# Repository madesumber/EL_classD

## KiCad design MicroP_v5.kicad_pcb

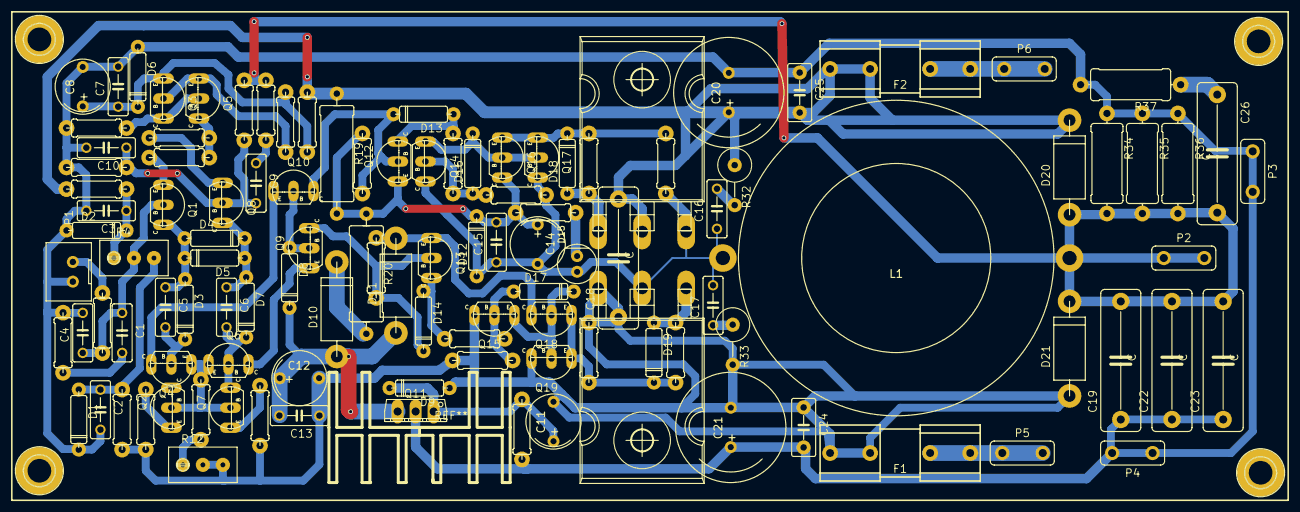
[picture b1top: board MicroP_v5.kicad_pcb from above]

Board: 2 copper layers, 114 parts (0 on the bottom side), 52 nets.

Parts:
C1, C2, C3, C4, C5, C6, C7, C9, C10, C13, C15, C16, C17: C; C050-025X075
C8, C11, C12, C14: CP; CP_5mm
C18, C19, C22, C23, C26: C; C-X2-150-054X183
C20, C21: CP; CP_5mm_14mm
C24, C25: C; C050-030X075
D1, D2, D6, D8, D9, D12: D_Schottky; DIODE_7.62mm
D3, D4, D5, D7, D13, D14, D16, D17, D18, D19: D; DIODE_7.62mm
D10, D11, D20, D21: D; Diode-3A
D15: Led_Small; LED
F1, F2: FUSE; Fuse-holder1
L1: INDUCTOR; Core_T157
P1: IN; CON-XH-2pin
P2, P3, P4, P5, P6: CONN_01X01; SKUN_TAB_PCB
Q1, Q3, Q5, Q8, Q12, Q13, Q14, Q15, Q17, Q19: BC557; TO92-321_EBC
Q2, Q4, Q6, Q7, Q9, Q10, Q16, Q18: BC547; TO92-321_EBC
Q11: TIP120; TO126V
Q20, Q21: IRF540N; TO247BH-123_GDS
R1, R2, R3, R5, R6, R7, R8, R9, R10, R11, R13, R14, R15, R16, R17, R18, R21, R22, R23, R24, R25, R26, R27, R28, R29, R30, R31: R; R0207-7
R4, R12: TRIM; R-TRIM3296W
R19, R20: R; R0414-15
R32, R33: R; R0617V
R34, R35, R36, R37: R; R0411-12

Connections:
GND: C2.2, C3.2, C4.2, C7.2, C8.2, C10.2, C19.1, C20.2, C21.1, C22.1, C23.1, C24.2, C25.1, D1.1, D2.2, D6.2, P1.1, P3.1, P4.1, Q11.2, R2.1, R6.1, R16.2, R18.1, R34.1, R35.1, R36.1, R37.2
unnamed: C1.1, C4.1, Q1.2, R1.2, R4.2
unnamed: C1.2, R2.2
unnamed: C2.1, D1.2, R4.3, R5.2
unnamed: C3.1, D2.1, R3.1, R4.1
unnamed: C5.1, D3.2, D4.2, D5.1, Q1.1
unnamed: C5.2, D3.1, Q2.1, Q4.2
unnamed: C6.1, D4.1, D5.2, D7.2, Q8.1
unnamed: C6.2, D7.1, Q6.2, Q7.1
unnamed: C7.1, C8.1, D6.1, Q3.3, R9.2, R10.2
unnamed: C9.1, R15.1
unnamed: C9.2, C10.1, Q8.2, R17.1, R18.2
unnamed: C11.1, D9.1, Q11.1, R16.1
unnamed: C11.2, C12.2, C13.1, C18.1, C21.2, C24.1, D9.2, D21.2, F1.1, Q15.1, Q19.1, Q21.3, R5.1, R7.1, R12.2, R12.3, R14.1, R27.2, R31.2, R33.2
unnamed: C12.1, C13.2, D8.1, D10.2, D11.2, Q11.3
unnamed: C14.1, C15.2, D12.1, Q12.3, Q16.1, R19.2, R20.1, R21.2, R22.1
unnamed: C14.2, C15.1, C16.1, C17.2, D12.2, D15.2, L1.1, Q14.1, Q17.1, Q20.3, Q21.2, R26.2, R30.2
unnamed: C16.2, R32.2
unnamed: C17.1, R33.1
unnamed: C18.2, C20.1, C25.2, D20.1, F2.1, Q20.2, R3.2, R9.1, R19.1, R32.1
unnamed: C19.2, C22.2, C23.2, C26.2, D20.2, D21.1, L1.2, P2.1, R15.2, R17.2, R34.2, R35.2, R36.2
unnamed: C26.1, R37.1
unnamed: D8.2, Q9.2, Q10.2
unnamed: D10.1, R20.2
unnamed: D11.1, Q13.3, Q18.1, R23.1
unnamed: D13.1, Q10.1, Q12.2, R22.2
unnamed: D13.2, Q12.1, R24.2
unnamed: D14.1, Q9.1, Q13.2, R23.2
unnamed: D14.2, Q13.1, R25.2
unnamed: D15.1, R21.1
unnamed: D16.1, Q14.3, Q16.2, Q17.2
unnamed: D16.2, Q14.2, R24.1, R26.1
unnamed: D17.1, Q15.3, Q18.2, Q19.2
unnamed: D17.2, Q15.2, R25.1, R27.1
unnamed: D18.1, Q16.3, Q17.3, R28.2, R30.1
unnamed: D18.2, Q20.1, R28.1
unnamed: D19.1, Q18.3, Q19.3, R29.2, R31.1
unnamed: D19.2, Q21.1, R29.1
unnamed: F1.2, P5.1
unnamed: F2.2, P6.1
unnamed: P1.2, R1.1
unnamed: Q1.3, R8.2
unnamed: Q2.2, Q4.3, Q6.3, Q7.2, R11.2
unnamed: Q2.3, R7.2
unnamed: Q3.1, Q5.2, R6.2
unnamed: Q3.2, Q5.3, R10.1
unnamed: Q5.1, R8.1, R13.2
unnamed: Q6.1, Q9.3
unnamed: Q7.3, R14.2
unnamed: Q8.3, R13.1
unnamed: Q4.1, Q10.3
unnamed: R11.1, R12.1
